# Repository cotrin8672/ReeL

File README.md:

# ReeL

Hardware sources and manufacturing assets for the ReeL split keyboard.

The RMK firmware, Vial definition, trackball profiler, and firmware build
workflow live in [rmk-config-ReeL](https://github.com/cotrin8672/rmk-config-ReeL).

## Repository layout

- `pcb/`: KiCad projects, project-local symbol and footprint libraries, and the PMW3610 breakout manufacturing package
- `model/`: mechanical STEP and STL models
- `fabrication/gerber/`: generated Gerber and drill outputs for the main left and right PCBs
- `docs/materials/`: component research and supporting material documents

The firmware repository was split from hardware commit
`b9bacc7681b5a1461f23b08cf7a2b1b867c73b0e`.

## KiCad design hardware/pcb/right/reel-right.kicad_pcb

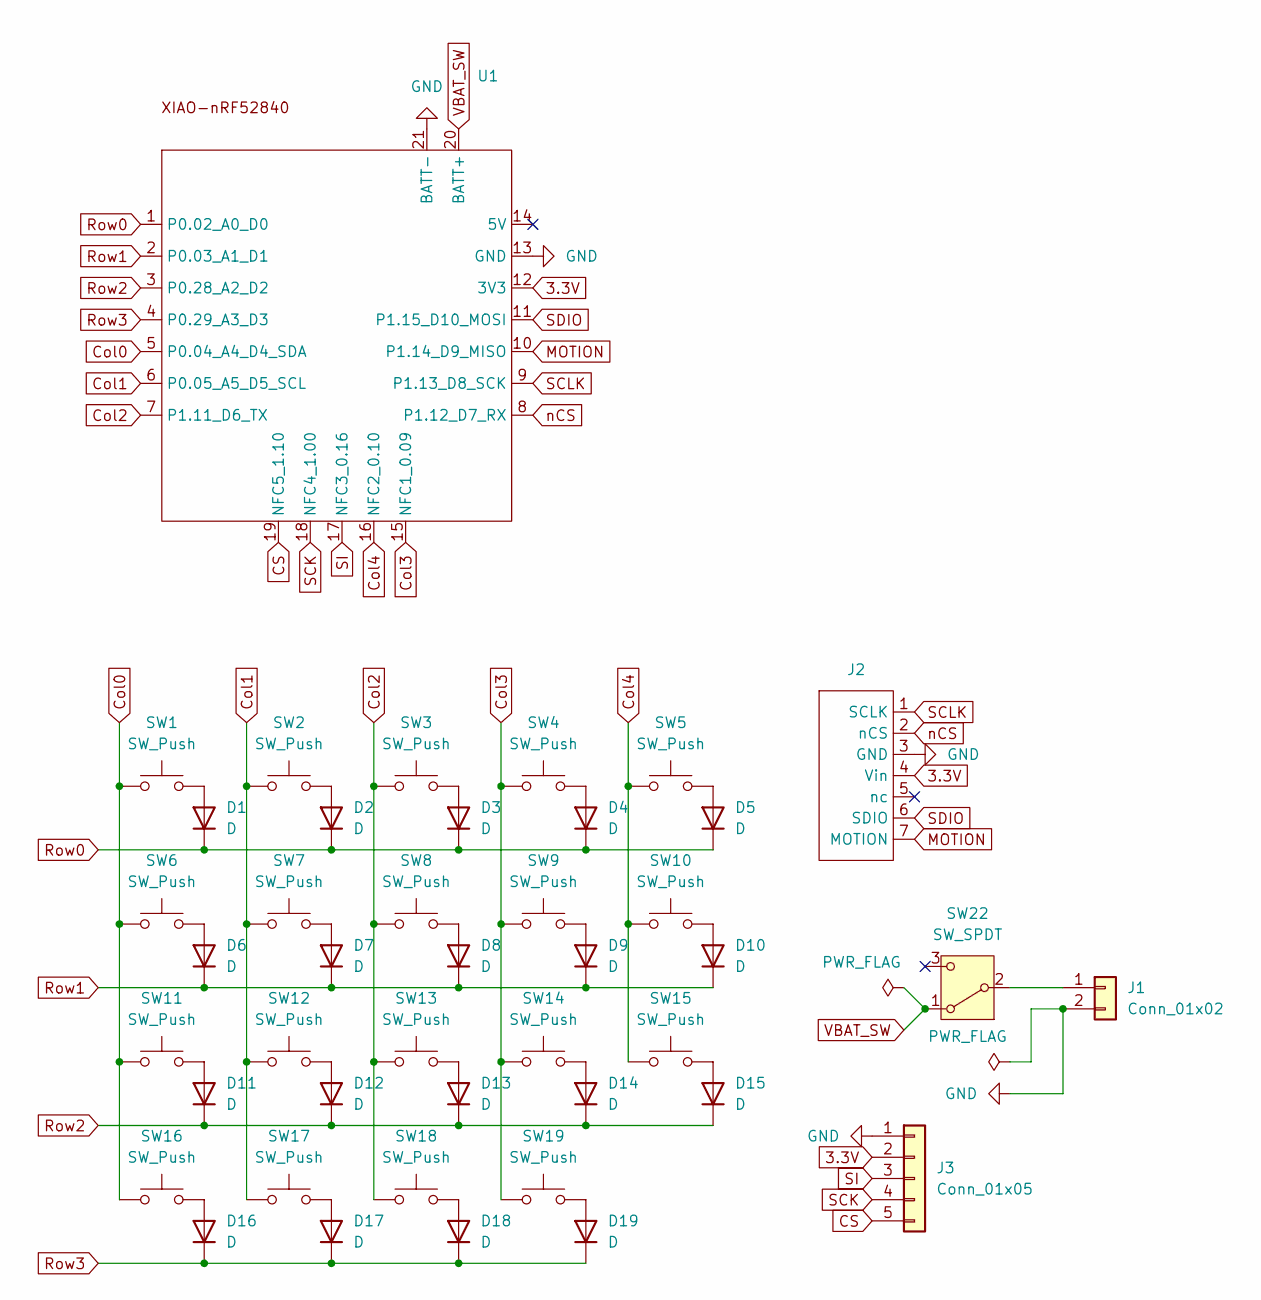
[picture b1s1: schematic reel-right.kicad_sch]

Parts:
D1, D2, D3, D4, D5, D6, D7, D8, D9, D10, D11, D12, D13, D14, D15, D16, D17, D18, D19: D; Diode_SMD
J1: Conn_01x02; JST_PH_S2B-PH-K_1x02_P2.00mm_Horizontal
J2: pmw3610_connector
J3: Conn_01x05; Display_BeeKeeb_MIP_1.08in_LS011B7DH03
SW1, SW2, SW3, SW4, SW5, SW6, SW7, SW8, SW9, SW10, SW11, SW12, SW13, SW14, SW15, SW16, SW17, SW18, SW19: SW_Push; SW_Hotswap_Kailh_Choc_V1V2_1.00u
SW22: SW_SPDT; SW_SPDT_PCM12
U1: XIAO_nRF52840_wBAT_wNFC_1

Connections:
3.3V: J2.4 (Vin), J3.2, U1.12 (3V3)
CS: J3.5, U1.19 (NFC5_1.10)
Col0: SW1.1, SW6.1, SW11.1, SW16.1, U1.5 (P0.04_A4_D4_SDA)
Col1: SW2.1, SW7.1, SW12.1, SW17.1, U1.6 (P0.05_A5_D5_SCL)
Col2: SW3.1, SW8.1, SW13.1, SW18.1, U1.7 (P1.11_D6_TX)
Col3: SW4.1, SW9.1, SW14.1, SW19.1, U1.15 (NFC1_0.09)
Col4: SW5.1, SW10.1, SW15.1, U1.16 (NFC2_0.10)
GND: J1.2, J2.3 (GND), J3.1, U1.13 (GND), U1.21 (BATT-)
MOTION: J2.7 (MOTION), U1.10 (P1.14_D9_MISO)
unnamed: D1.2 (A), SW1.2
unnamed: D2.2 (A), SW2.2
unnamed: D3.2 (A), SW3.2
unnamed: D4.2 (A), SW4.2
unnamed: D5.2 (A), SW5.2
unnamed: D6.2 (A), SW6.2
unnamed: D7.2 (A), SW7.2
unnamed: D8.2 (A), SW8.2
unnamed: D9.2 (A), SW9.2
unnamed: D10.2 (A), SW10.2
unnamed: D11.2 (A), SW11.2
unnamed: D12.2 (A), SW12.2
unnamed: D13.2 (A), SW13.2
unnamed: D14.2 (A), SW14.2
unnamed: D15.2 (A), SW15.2
unnamed: D16.2 (A), SW16.2
unnamed: D17.2 (A), SW17.2
unnamed: D18.2 (A), SW18.2
unnamed: D19.2 (A), SW19.2
unnamed: J1.1, SW22.2 (B)
Row0: D1.1 (K), D2.1 (K), D3.1 (K), D4.1 (K), D5.1 (K), U1.1 (P0.02_A0_D0)
Row1: D6.1 (K), D7.1 (K), D8.1 (K), D9.1 (K), D10.1 (K), U1.2 (P0.03_A1_D1)
Row2: D11.1 (K), D12.1 (K), D13.1 (K), D14.1 (K), D15.1 (K), U1.3 (P0.28_A2_D2)
Row3: D16.1 (K), D17.1 (K), D18.1 (K), D19.1 (K), U1.4 (P0.29_A3_D3)
SCK: J3.4, U1.18 (NFC4_1.00)
SCLK: J2.1 (SCLK), U1.9 (P1.13_D8_SCK)
SDIO: J2.6 (SDIO), U1.11 (P1.15_D10_MOSI)
SI: J3.3, U1.17 (NFC3_0.16)
VBAT_SW: SW22.1 (A), U1.20 (BATT+)
nCS: J2.2 (nCS), U1.8 (P1.12_D7_RX)

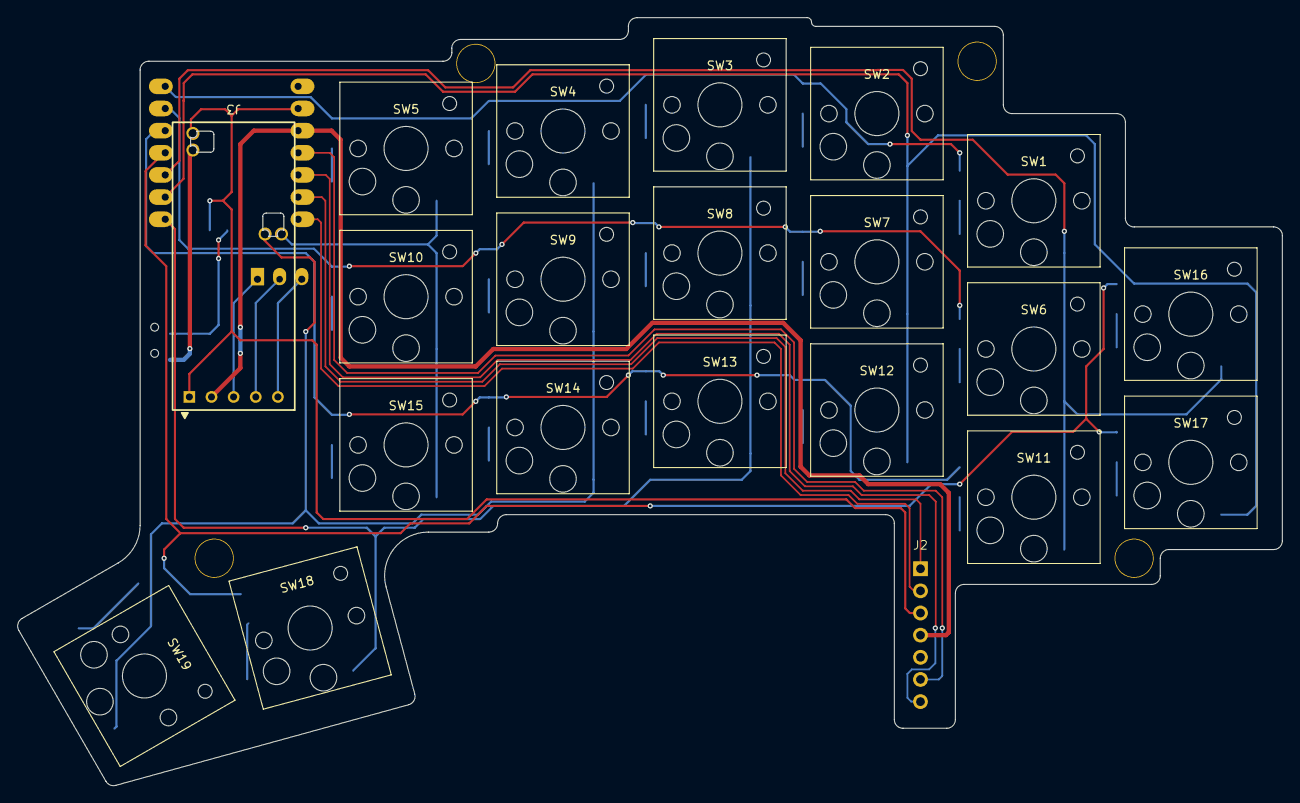
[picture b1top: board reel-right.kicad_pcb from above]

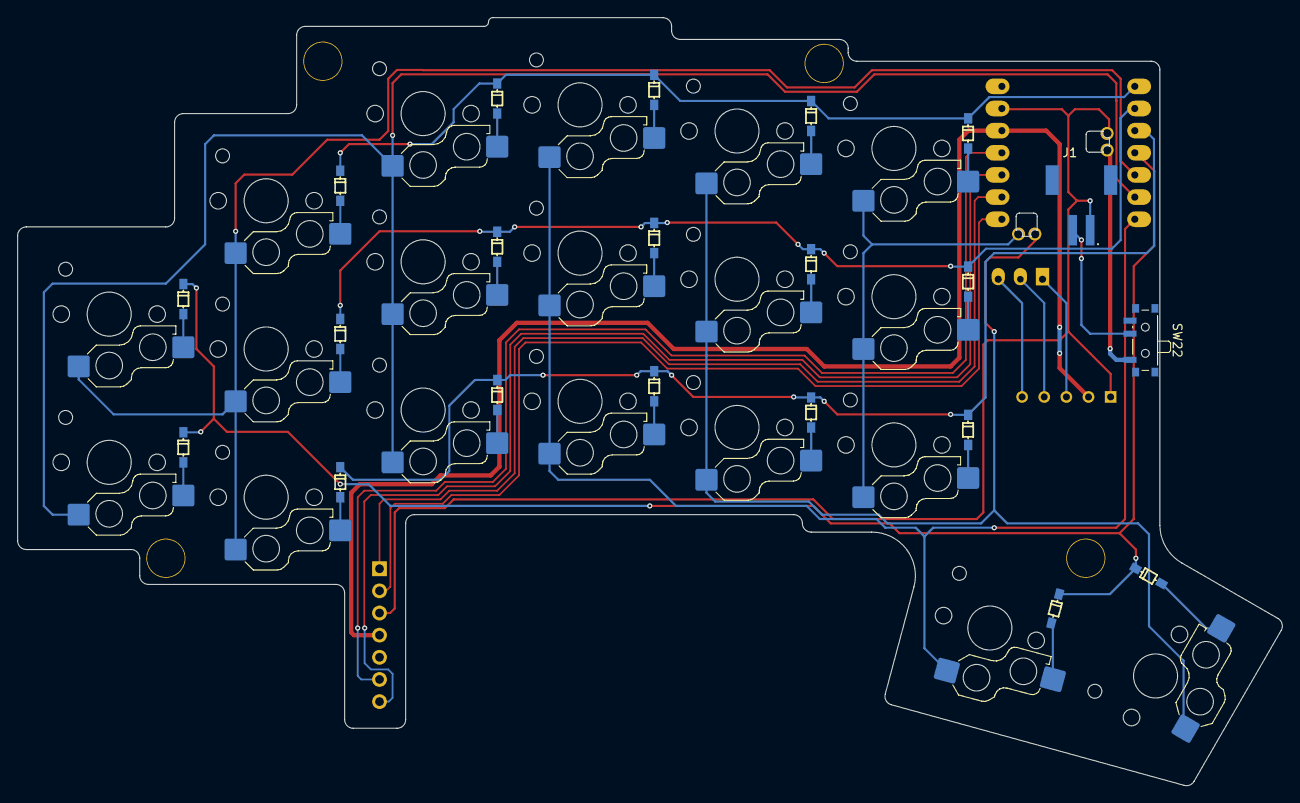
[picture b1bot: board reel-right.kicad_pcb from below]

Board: 2 copper layers, 145.0 x 88.1 mm, 47 parts (2 on the bottom side), 39 nets.

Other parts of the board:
Ref**: Val**; m2_Spacer_Hole
Ref**#2, Ref**#3, Ref**#4: Val**; m2_Spacer_Hole

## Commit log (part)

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2026-05-19 remove: .history
2026-06-17 change matrix and add rotary encoder in scketch
2026-06-17 footprints
2026-06-17 generated PCB
2026-06-18 edit pcb
2026-06-18 edit outline
2026-06-27 Update left board encoder footprint
2026-06-27 Update left board assets
